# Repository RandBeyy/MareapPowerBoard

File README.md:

STM32F103C8 (blue pill) based project. Main purpose is to build a testing power board for some selfmade devices. It can show power consumption of USB devices and diagnose some errors.

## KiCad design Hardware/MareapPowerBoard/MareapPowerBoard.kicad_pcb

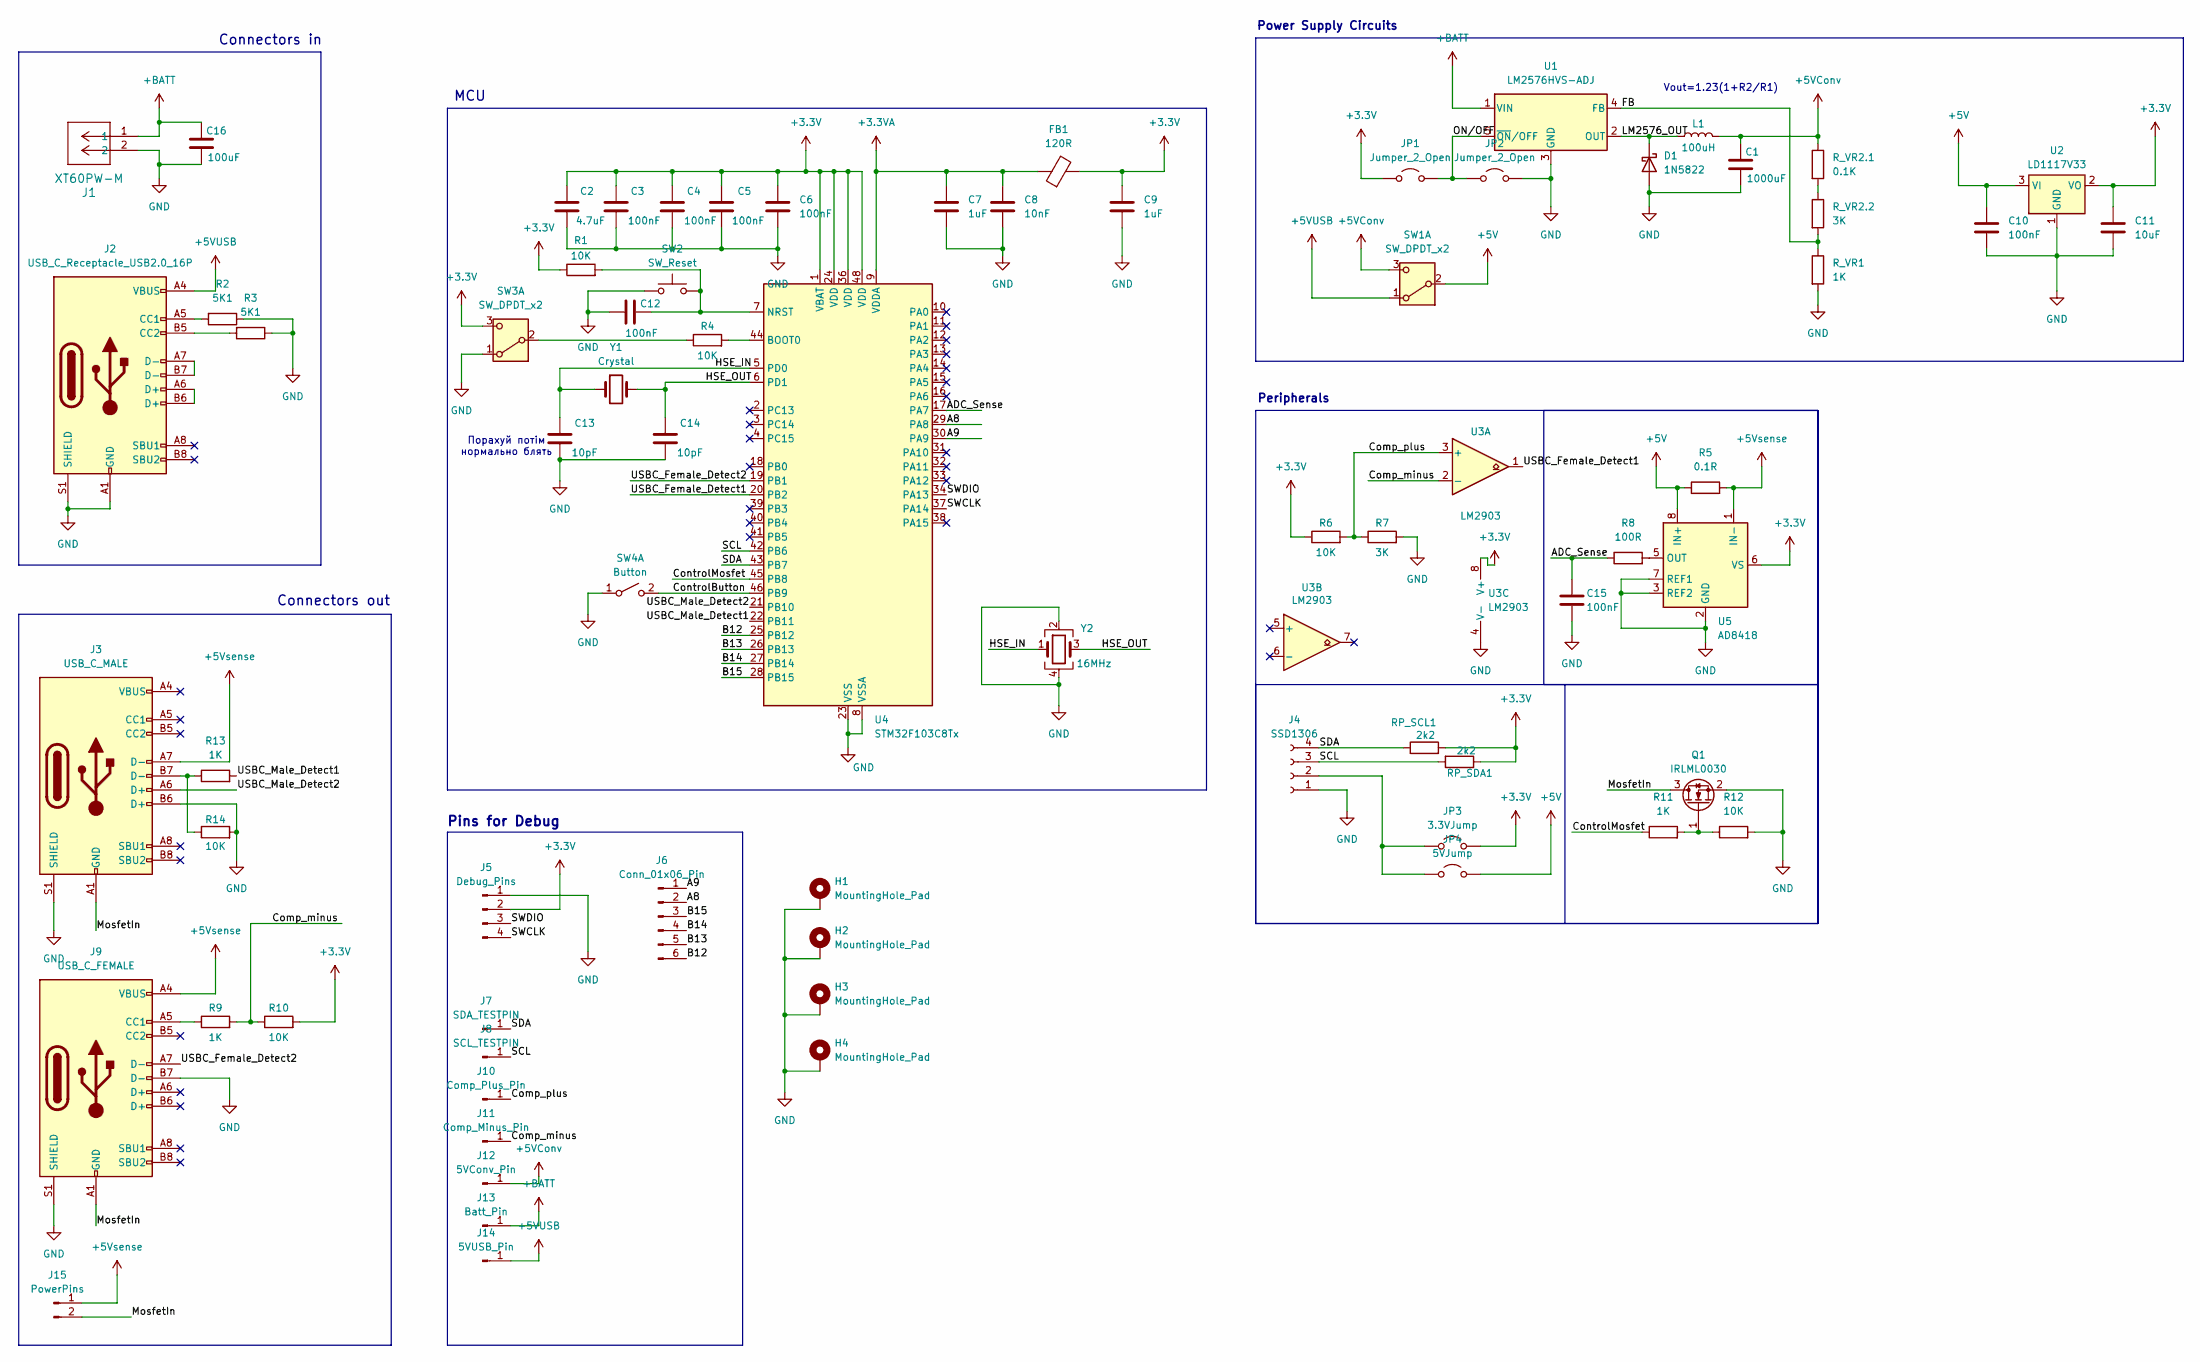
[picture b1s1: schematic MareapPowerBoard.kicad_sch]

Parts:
C1: 1000uF; CP_Radial_D8.0mm_P3.50mm
C2: 4.7uF; C_0603_1608Metric
C3, C4, C5, C6, C10, C12, C15: 100nF; C_0603_1608Metric
C7, C9: 1uF; C_0603_1608Metric
C8: 10nF; C_0603_1608Metric
C11: 10uF; C_0603_1608Metric
C13, C14: 10pF; C_0603_1608Metric
C16: 100uF; CP_Radial_D8.0mm_P3.50mm
D1: 1N5822; D_DO-201AD_P15.24mm_Horizontal
FB1: 120R; C_0603_1608Metric
H1, H2, H3, H4: MountingHole_Pad; MountingHole_2.5mm_Pad_TopOnly
J1: XT60PW-M; CONN_XT60PW-M_AMA
J2: USB_C_Receptacle_USB2.0_16P; USB_C_Receptacle_HCTL_HC-TYPE-C-16P-01A
J3: USB_C_MALE; USB_C_Plug_Male_16P_SMD11.9_Vertical
J4: SSD1306; SSD1306_0.96_Oled
J5: Debug_Pins; PinHeader_1x04_P2.54mm_Vertical
J6: Conn_01x06_Pin; PinHeader_1x06_P2.00mm_Vertical
J7: SDA_TESTPIN; PinHeader_1x01_P2.00mm_Vertical
J8: SCL_TESTPIN; PinHeader_1x01_P2.00mm_Vertical
J9: USB_C_FEMALE; USB_C_Receptacle_HCTL_HC-TYPE-C-16P-01A
J10: Comp_Plus_Pin; PinHeader_1x01_P2.00mm_Vertical
J11: Comp_Minus_Pin; PinHeader_1x01_P2.00mm_Vertical
J12: 5VConv_Pin; PinHeader_1x01_P2.00mm_Vertical
J13: Batt_Pin; PinHeader_1x01_P2.00mm_Vertical
J14: 5VUSB_Pin; PinHeader_1x01_P2.00mm_Vertical
J15: PowerPins; PinHeader_1x02_P2.54mm_Vertical
JP1, JP2: Jumper_2_Open; SolderJumper-2_P1.3mm_Open_RoundedPad1.0x1.5mm
JP3: 3.3VJump; SolderJumper-2_P1.3mm_Open_RoundedPad1.0x1.5mm
JP4: 5VJump; SolderJumper-2_P1.3mm_Open_RoundedPad1.0x1.5mm
L1: 100uH; SND0705
Q1: IRLML0030; SOT-23
R1, R4, R6, R10, R12, R14: 10K; R_0603_1608Metric
R2, R3: 5K1; R_0603_1608Metric
R5: 0.1R; R_2512_6332Metric_Pad1.40x3.35mm_HandSolder
R7: 3K; R_0603_1608Metric
R8: 100R; R_0603_1608Metric
R9, R11, R13: 1K; R_0603_1608Metric
RP_SCL1: 2k2; R_0402_1005Metric
RP_SDA1: 2k2; R_0402_1005Metric
R_VR1: 1K; R_0603_1608Metric
R_VR2.1: 0.1K; R_0603_1608Metric
R_VR2.2: 3K; R_0603_1608Metric
SW1, SW3: SW_DPDT_x2; SW_Slide_SPDT_Angled_CK_OS102011MA1Q
SW2: SW_Reset; SW_SPST_PTS810
SW4: Button; SW_SPST_PTS810
U1: LM2576HVS-ADJ; TO-263-5_TabPin3
U2: LD1117V33; SOT-223
U3: LM2903; SO-8_3.9x4.9mm_P1.27mm
U4: STM32F103C8Tx; LQFP-48_7x7mm_P0.5mm
U5: AD8418; SO-8_3.9x4.9mm_P1.27mm
Y1: Crystal; Crystal_HC49-4H_Vertical
Y2: 16MHz; Crystal_SMD_3225-4Pin_3.2x2.5mm

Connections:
+3.3V: C2.1, C3.1, C4.1, C5.1, C6.1, C9.1, C11.1, FB1.2, J5.2, JP1.1 (A), JP3.2 (B), R1.1, R6.1, R10.2, RP_SCL1.2, RP_SDA1.1, SW3.3 (C), U2.2 (VO), U3.8 (V+), U4.1 (VBAT), U4.24 (VDD), U4.36 (VDD), U4.48 (VDD), U5.6 (VS)
+3.3VA: C7.1, C8.1, FB1.1, U4.9 (VDDA)
+5V: C10.1, JP4.2 (B), R5.1, SW1.2 (B), U2.3 (VI), U5.8 (IN+)
+5VConv: C1.1, J12.1 (Pin_1_1), L1.2, R_VR2.1.1, SW1.3 (C)
+5VUSB: J2.A4 (VBUS), J2.A9 (VBUS), J2.B4 (VBUS), J2.B9 (VBUS), J14.1 (Pin_1_1), SW1.1 (A)
+5Vsense: J3.A7 (D-), J9.A4 (VBUS), J9.A9 (VBUS), J9.B4 (VBUS), J9.B9 (VBUS), J15.1, R5.2, U5.1 (IN-)
+BATT: C16.1, J1.1, J13.1 (Pin_1_1), U1.1 (VIN)
/A8: J6.2, U4.29 (PA8)
/A9: J6.1, U4.30 (PA9)
/ADC_Sense: C15.1, R8.1, U4.17 (PA7)
/B12: J6.6, U4.25 (PB12)
/B13: J6.5, U4.26 (PB13)
/B14: J6.4, U4.27 (PB14)
/B15: J6.3, U4.28 (PB15)
/Comp_minus: J11.1 (Pin_1_1), R9.2, R10.1, U3.2 (-)
/Comp_plus: J10.1 (Pin_1_1), R6.2, R7.1, U3.3 (+)
/ControlButton: SW4.2 (B), U4.46 (PB9)
/ControlMosfet: R11.1, U4.45 (PB8)
/FB: R_VR1.1, R_VR2.2.2, U1.4 (FB)
/HSE_IN: C13.1, U4.5 (PD0), Y1.1, Y2.1
/HSE_OUT: C14.1, U4.6 (PD1), Y1.2, Y2.3
/LM2576_OUT: D1.1 (K), L1.1, U1.2 (OUT)
/MosfetIn: J3.A1 (GND), J3.A12 (GND), J3.B1 (GND), J3.B12 (GND), J9.A1 (GND), J9.A12 (GND), J9.B1 (GND), J9.B12 (GND), J15.2, Q1.3 (D)
/ON/OFF: JP1.2 (B), JP2.1 (A), U1.5 (~ON/OFF)
/SCL: J4.3, J8.1 (Pin_1_1), RP_SDA1.2, U4.42 (PB6)
/SDA: J4.4, J7.1 (Pin_1_1), RP_SCL1.1, U4.43 (PB7)
/SWCLK: J5.4, U4.37 (PA14)
/SWDIO: J5.3, U4.34 (PA13)
/USBC_Female_Detect1: U3.1, U4.20 (PB2)
/USBC_Female_Detect2: J9.A7 (D-), U4.19 (PB1)
/USBC_Male_Detect1: R13.2, U4.22 (PB11)
/USBC_Male_Detect2: J3.A6 (D+), U4.21 (PB10)
GND: C1.2, C2.2, C3.2, C4.2, C5.2, C6.2, C7.2, C8.2, C9.2, C10.2, C11.2, C12.1, C13.2, C14.2, C15.2, C16.2, D1.2 (A), H1.1 (1_1), H2.1 (1_1), H3.1 (1_1), H4.1 (1_1), J1.2, J2.A1 (GND), J2.A12 (GND), J2.B1 (GND), J2.B12 (GND), J2.S1 (SHIELD), J3.B6 (D+), J3.S1 (SHIELD), J4.1, J5.1, J9.B7 (D-), J9.S1 (SHIELD), JP2.2 (B), Q1.2 (S), R2.1, R3.1, R7.2, R12.2, R14.2, R_VR1.2, SW2.1, SW3.1 (A), SW4.1 (A), U1.3 (GND), U2.1 (GND), U3.4 (V-), U4.8 (VSSA), U4.23 (VSS), U4.35 (VSS), U4.47 (VSS), U5.2 (GND), U5.3 (REF2), U5.7 (REF1), Y2.2, Y2.4
unnamed: J2.A5 (CC1), R2.2
unnamed: J2.B5 (CC2), R3.2
unnamed: J2.A6 (D+), J2.B6 (D+)
unnamed: J2.A7 (D-), J2.B7 (D-)
unnamed: J3.B7 (D-), R13.1, R14.1
unnamed: J4.2, JP3.1 (A), JP4.1 (A)
unnamed: J9.A5 (CC1), R9.1
unnamed: Q1.1 (G), R11.2, R12.1
unnamed: R_VR2.1.2, R_VR2.2.1
unnamed: R4.1, SW3.2 (B)
unnamed: R4.2, U4.44 (BOOT0)
unnamed: C12.2, R1.2, SW2.2, U4.7 (NRST)
unnamed: R8.2, U5.5 (OUT)

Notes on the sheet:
Connectors in
Pins for Debug
Power Supply Сircuits
Порахуй потім нормально блять
Vout=1.23(1+R2/R1)
MCU
Peripherals
Connectors out

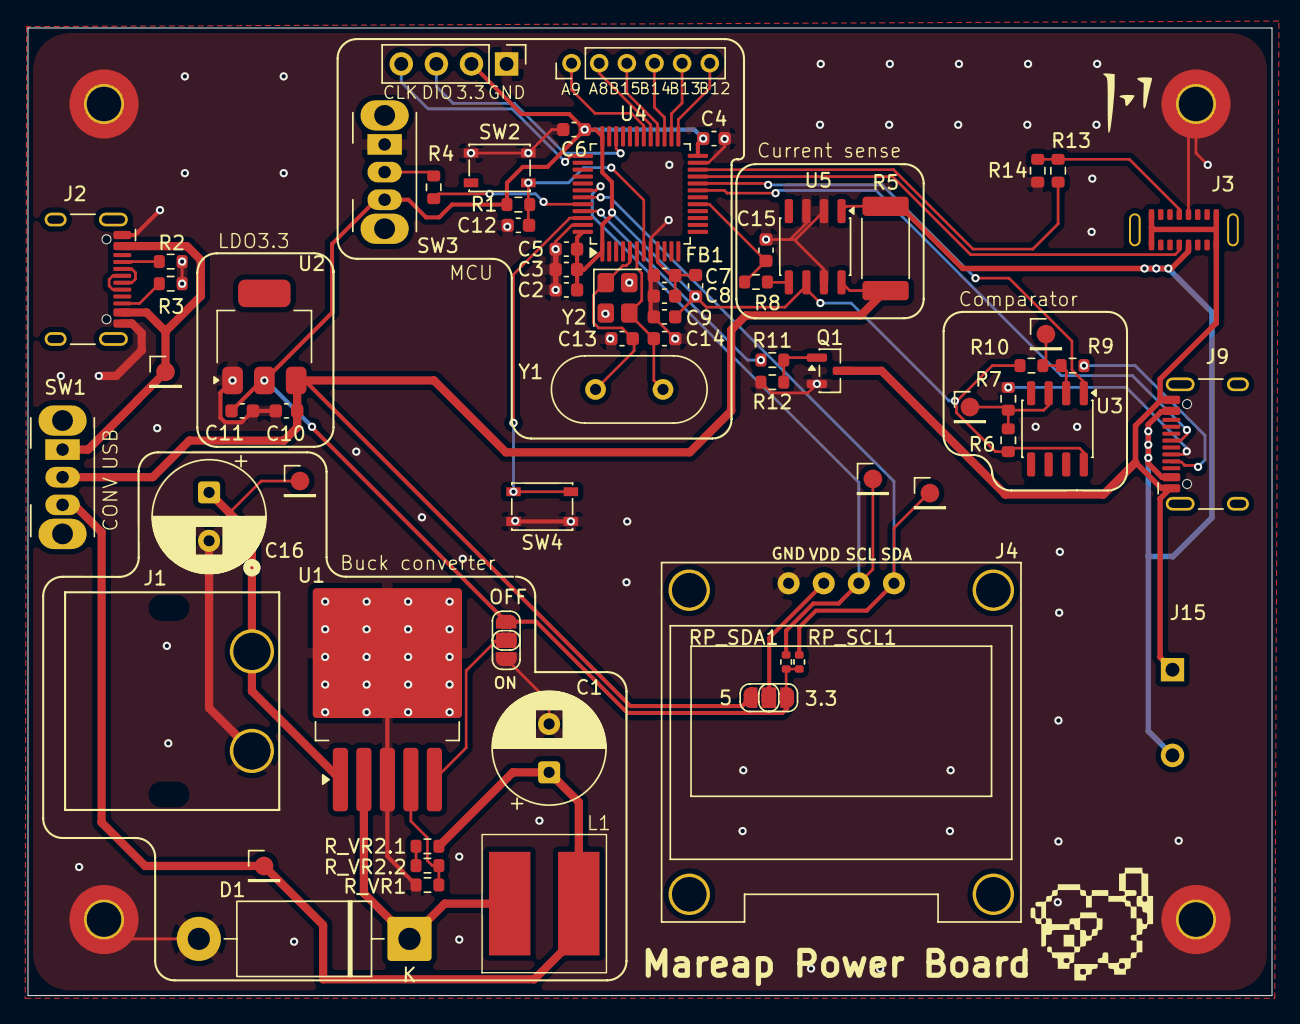
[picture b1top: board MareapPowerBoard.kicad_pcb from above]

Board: 2 copper layers, 90.0 x 70.0 mm, 73 parts (0 on the bottom side), 46 nets.

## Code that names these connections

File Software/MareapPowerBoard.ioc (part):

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Mcu.Name=STM32F103C(8-B)Tx
Mcu.Package=LQFP48
Mcu.UserName=STM32F103C8Tx
PA13.Mode=Serial_Wire
PA13.Signal=SYS_JTMS-SWDIO
PA14.Mode=Serial_Wire
PA14.Signal=SYS_JTCK-SWCLK
PA7.Signal=ADCx_IN7
PB1.Signal=GPIO_Input
PB10.Signal=GPIO_Input
PB11.Signal=GPIO_Input
PB2.Signal=GPIO_Input
PB6.Mode=I2C
PB6.Signal=I2C1_SCL
PB7.Mode=I2C
PB7.Signal=I2C1_SDA
PB8.Signal=GPIO_Output
PB9.Signal=GPIO_Input
PD0-OSC_IN.Mode=HSE-External-Oscillator
PD0-OSC_IN.Signal=RCC_OSC_IN
PD1-OSC_OUT.Mode=HSE-External-Oscillator
PD1-OSC_OUT.Signal=RCC_OSC_OUT
RCC.SYSCLKFreq_VALUE=72000000
RCC.SYSCLKSource=RCC_SYSCLKSOURCE_PLLCLK
board=custom

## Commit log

2026-05-20 basic error handler
2026-05-20 now device can handle 3 most frequent errors
2026-06-03 added missing connection and r14 for noise filtering
2026-06-03 added README.md
